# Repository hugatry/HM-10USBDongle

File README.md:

# HM10USBDongle
 USB dongle which includes HM-10 BLE module and CH330 USB-to-UART converter
## Video
 Show and tell video of this project:
 https://youtu.be/3KyHKgkS-Iw

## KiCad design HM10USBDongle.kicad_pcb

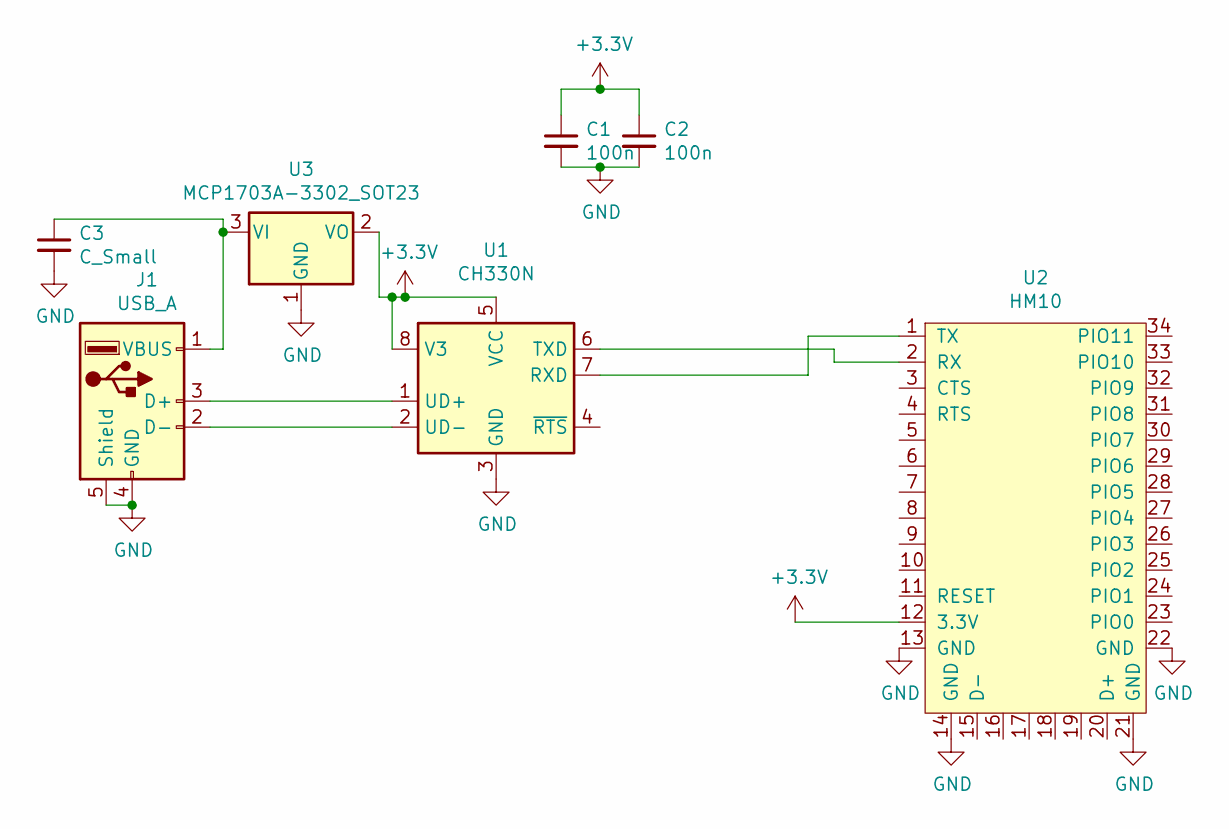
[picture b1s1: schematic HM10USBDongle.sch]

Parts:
C1, C2: 100n; C_0603_1608Metric
C3: C_Small; C_0603_1608Metric
J1: USB_A; USB-A-H
U1: CH330N; SOIC-8_3.9x4.9mm_P1.27mm
U2: HM10
U3: MCP1703A-3302_SOT23; SOT-23

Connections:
+3V3: C1.1, C2.1, U1.5 (VCC), U1.8 (V3), U2.12 (3.3V), U3.2 (VO)
GND: C1.2, C2.2, C3.2, J1.4 (GND), J1.5 (Shield), U1.3 (GND), U2.13 (GND), U2.14 (GND), U2.21 (GND), U2.22 (GND), U3.1 (GND)
unnamed: C3.1, J1.1 (VBUS), U3.3 (VI)
unnamed: J1.2 (D-), U1.2 (UD-)
unnamed: J1.3 (D+), U1.1 (UD+)
unnamed: U1.6 (TXD), U2.2 (RX)
unnamed: U1.7 (RXD), U2.1 (TX)

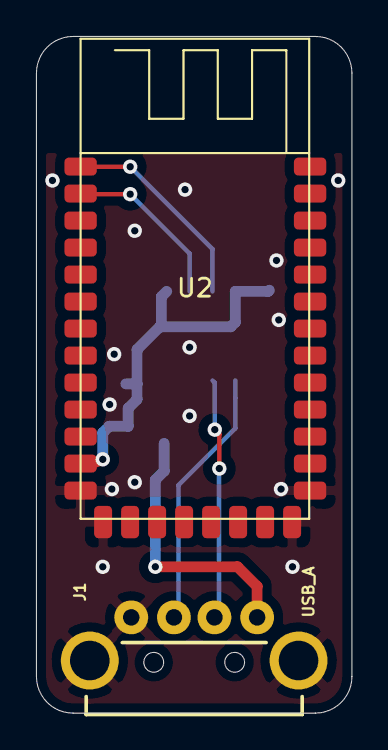
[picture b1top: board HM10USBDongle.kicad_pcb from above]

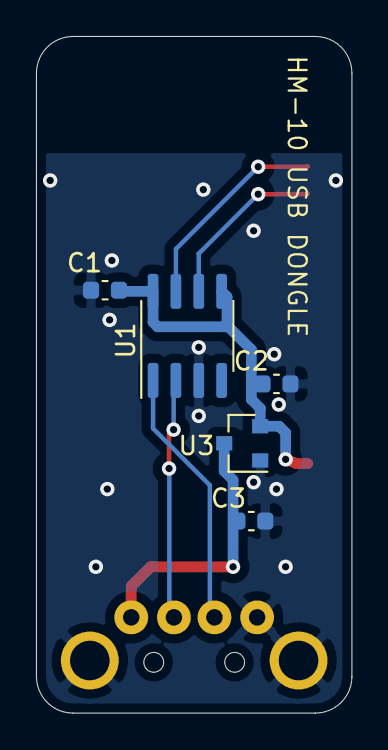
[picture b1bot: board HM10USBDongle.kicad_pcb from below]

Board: 2 copper layers, 17.5 x 37.6 mm, 7 parts (5 on the bottom side), 7 nets.
